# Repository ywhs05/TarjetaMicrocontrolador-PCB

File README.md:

# TarjetaMicrocontrolador-PCB

### Descripción
PCB que facilita la conexión con el microcontrolador LAUNCHXL-F28379D.

Proyecto del laboratorio LabCES de la Universidad de Costa Rica.

Permite facilitar la conexión con el microcontrolador LAUNCHXL-F28379D con las otras placas modulares:
- [Tarjeta digital a fibra óptica (DaFO)](https://github.com/ywhs05/DigitalToFiberOpticConverter-PCB)
- [Tarjeta sensor](https://github.com/ywhs05/TarjetaSensor-PCB)

Esta PCB es la tarjeta principal del sistema modular, tendrá la alimentación para las placas y el microcontrolador.

### Soporte
- y.huang@ucr.ac.cr
- mauricio.espinoza_bola@ucr.ac.cr

### Estado del proyecto

Se encuentra proceso de revisión en la etapa del diagrama esquemático y PCB.

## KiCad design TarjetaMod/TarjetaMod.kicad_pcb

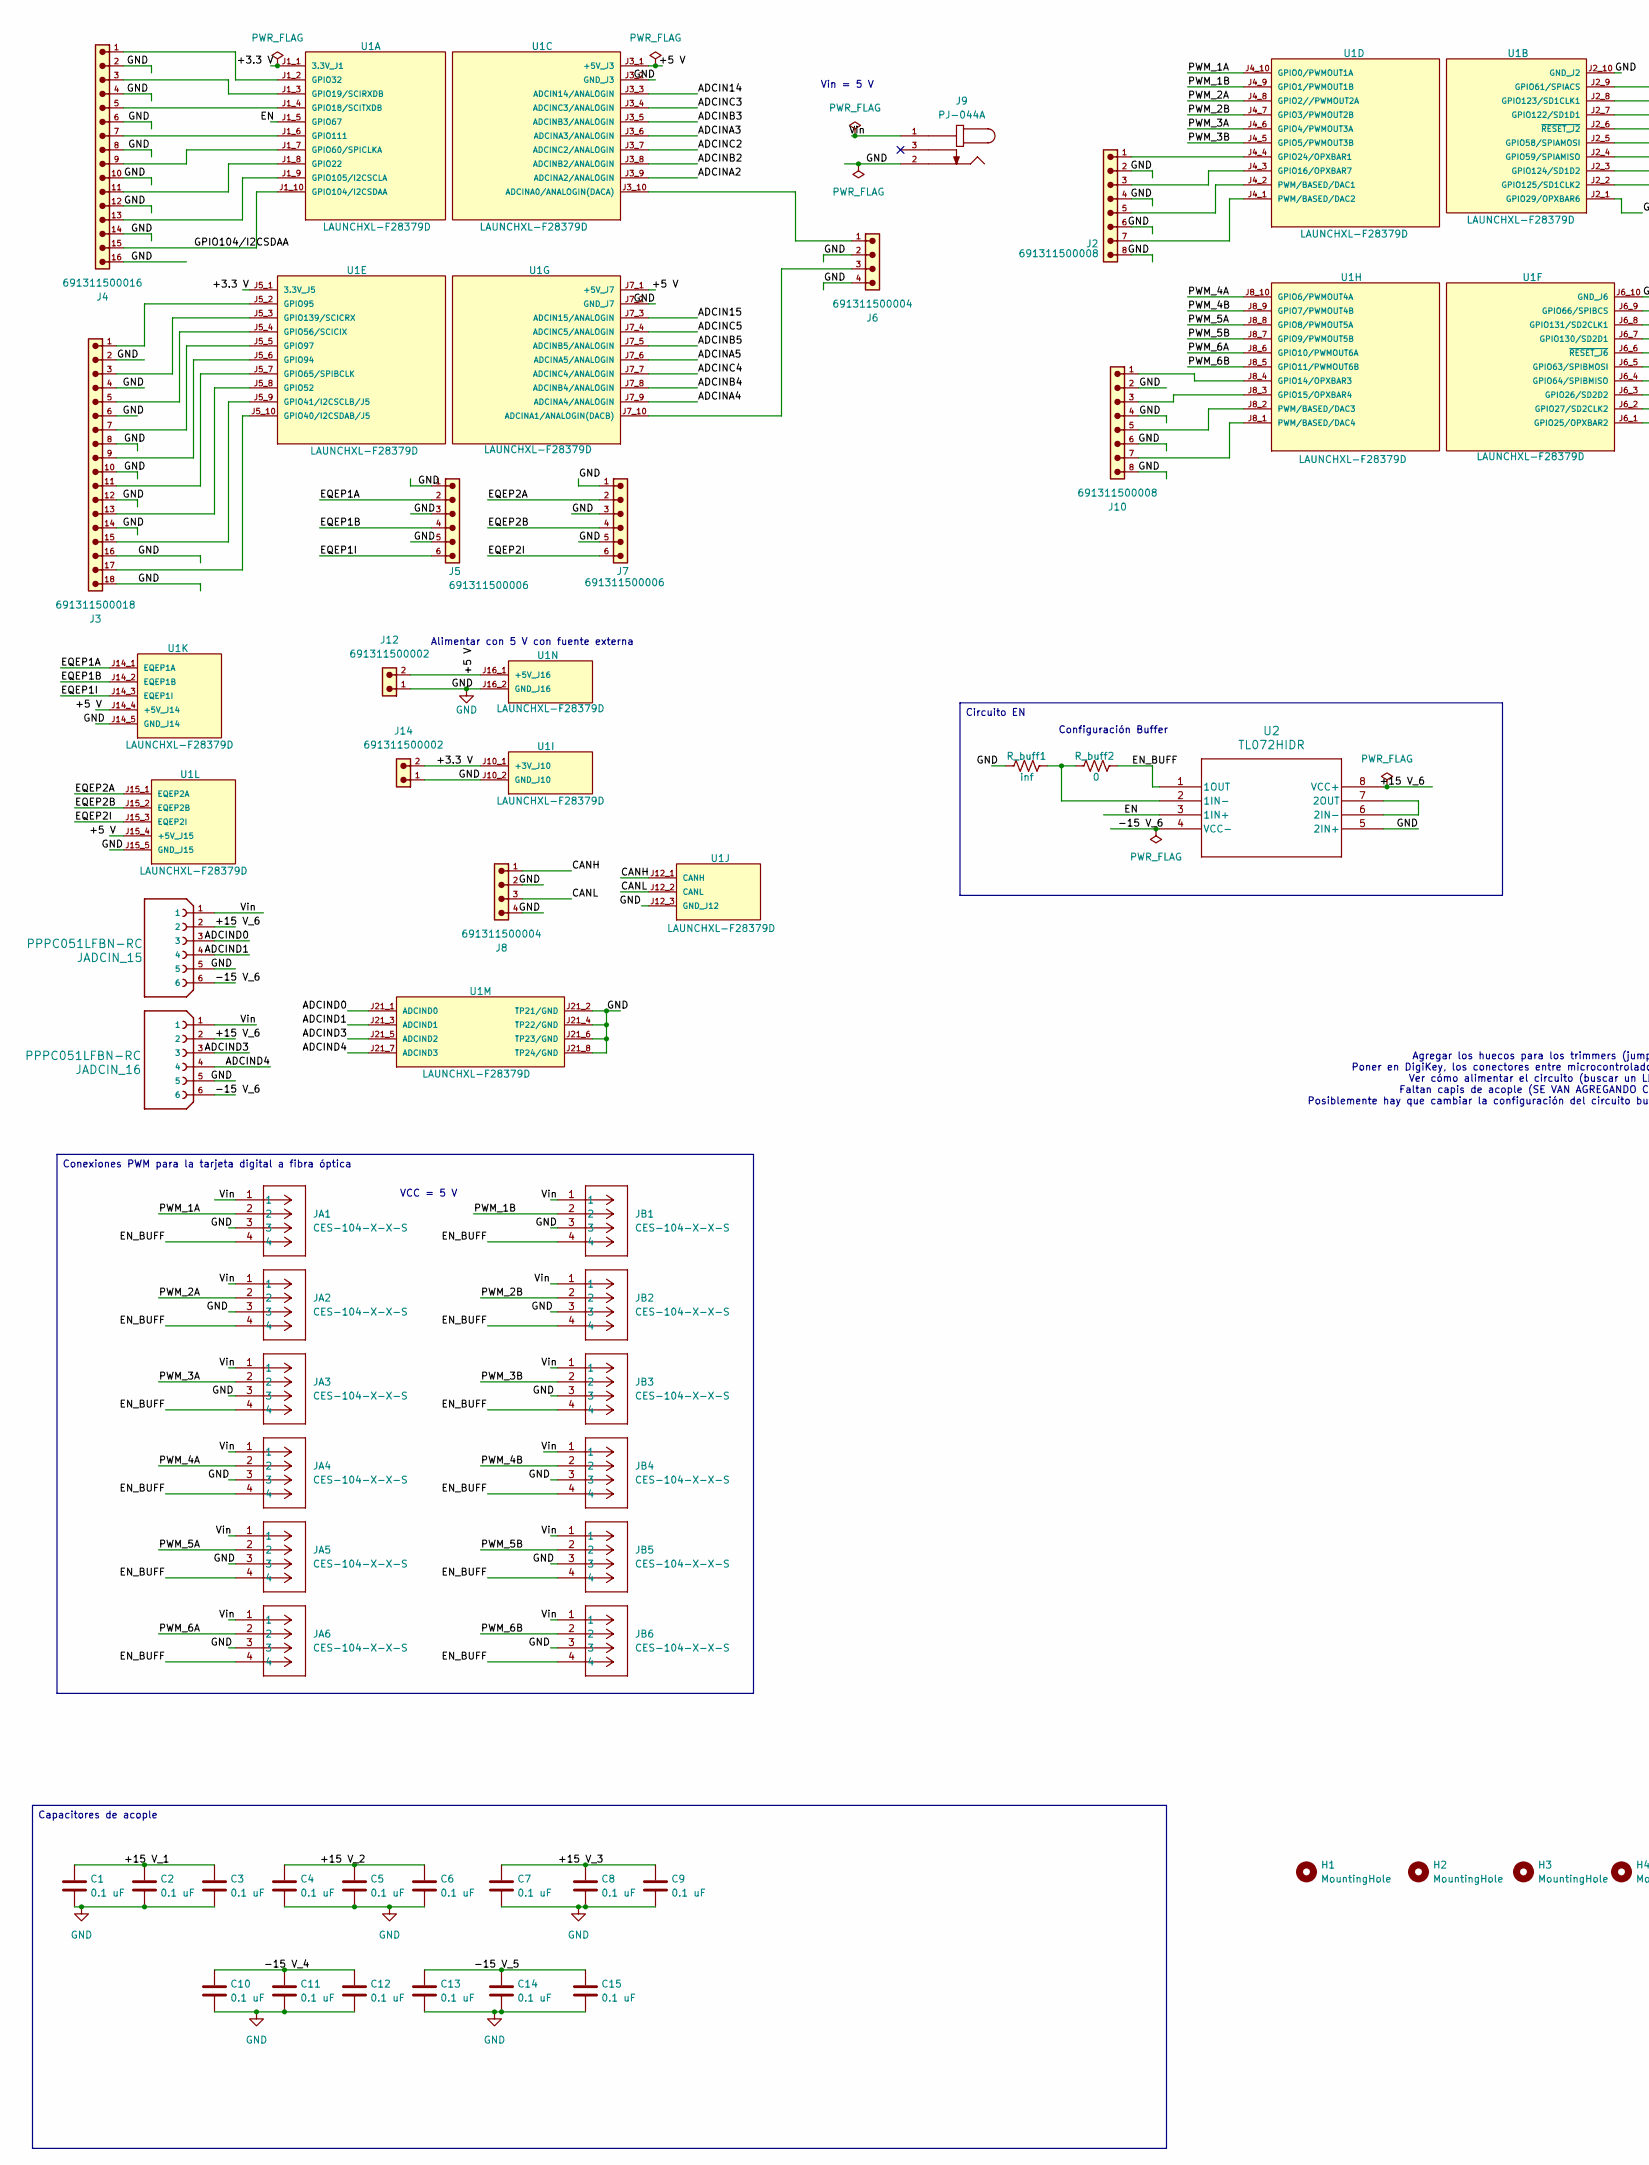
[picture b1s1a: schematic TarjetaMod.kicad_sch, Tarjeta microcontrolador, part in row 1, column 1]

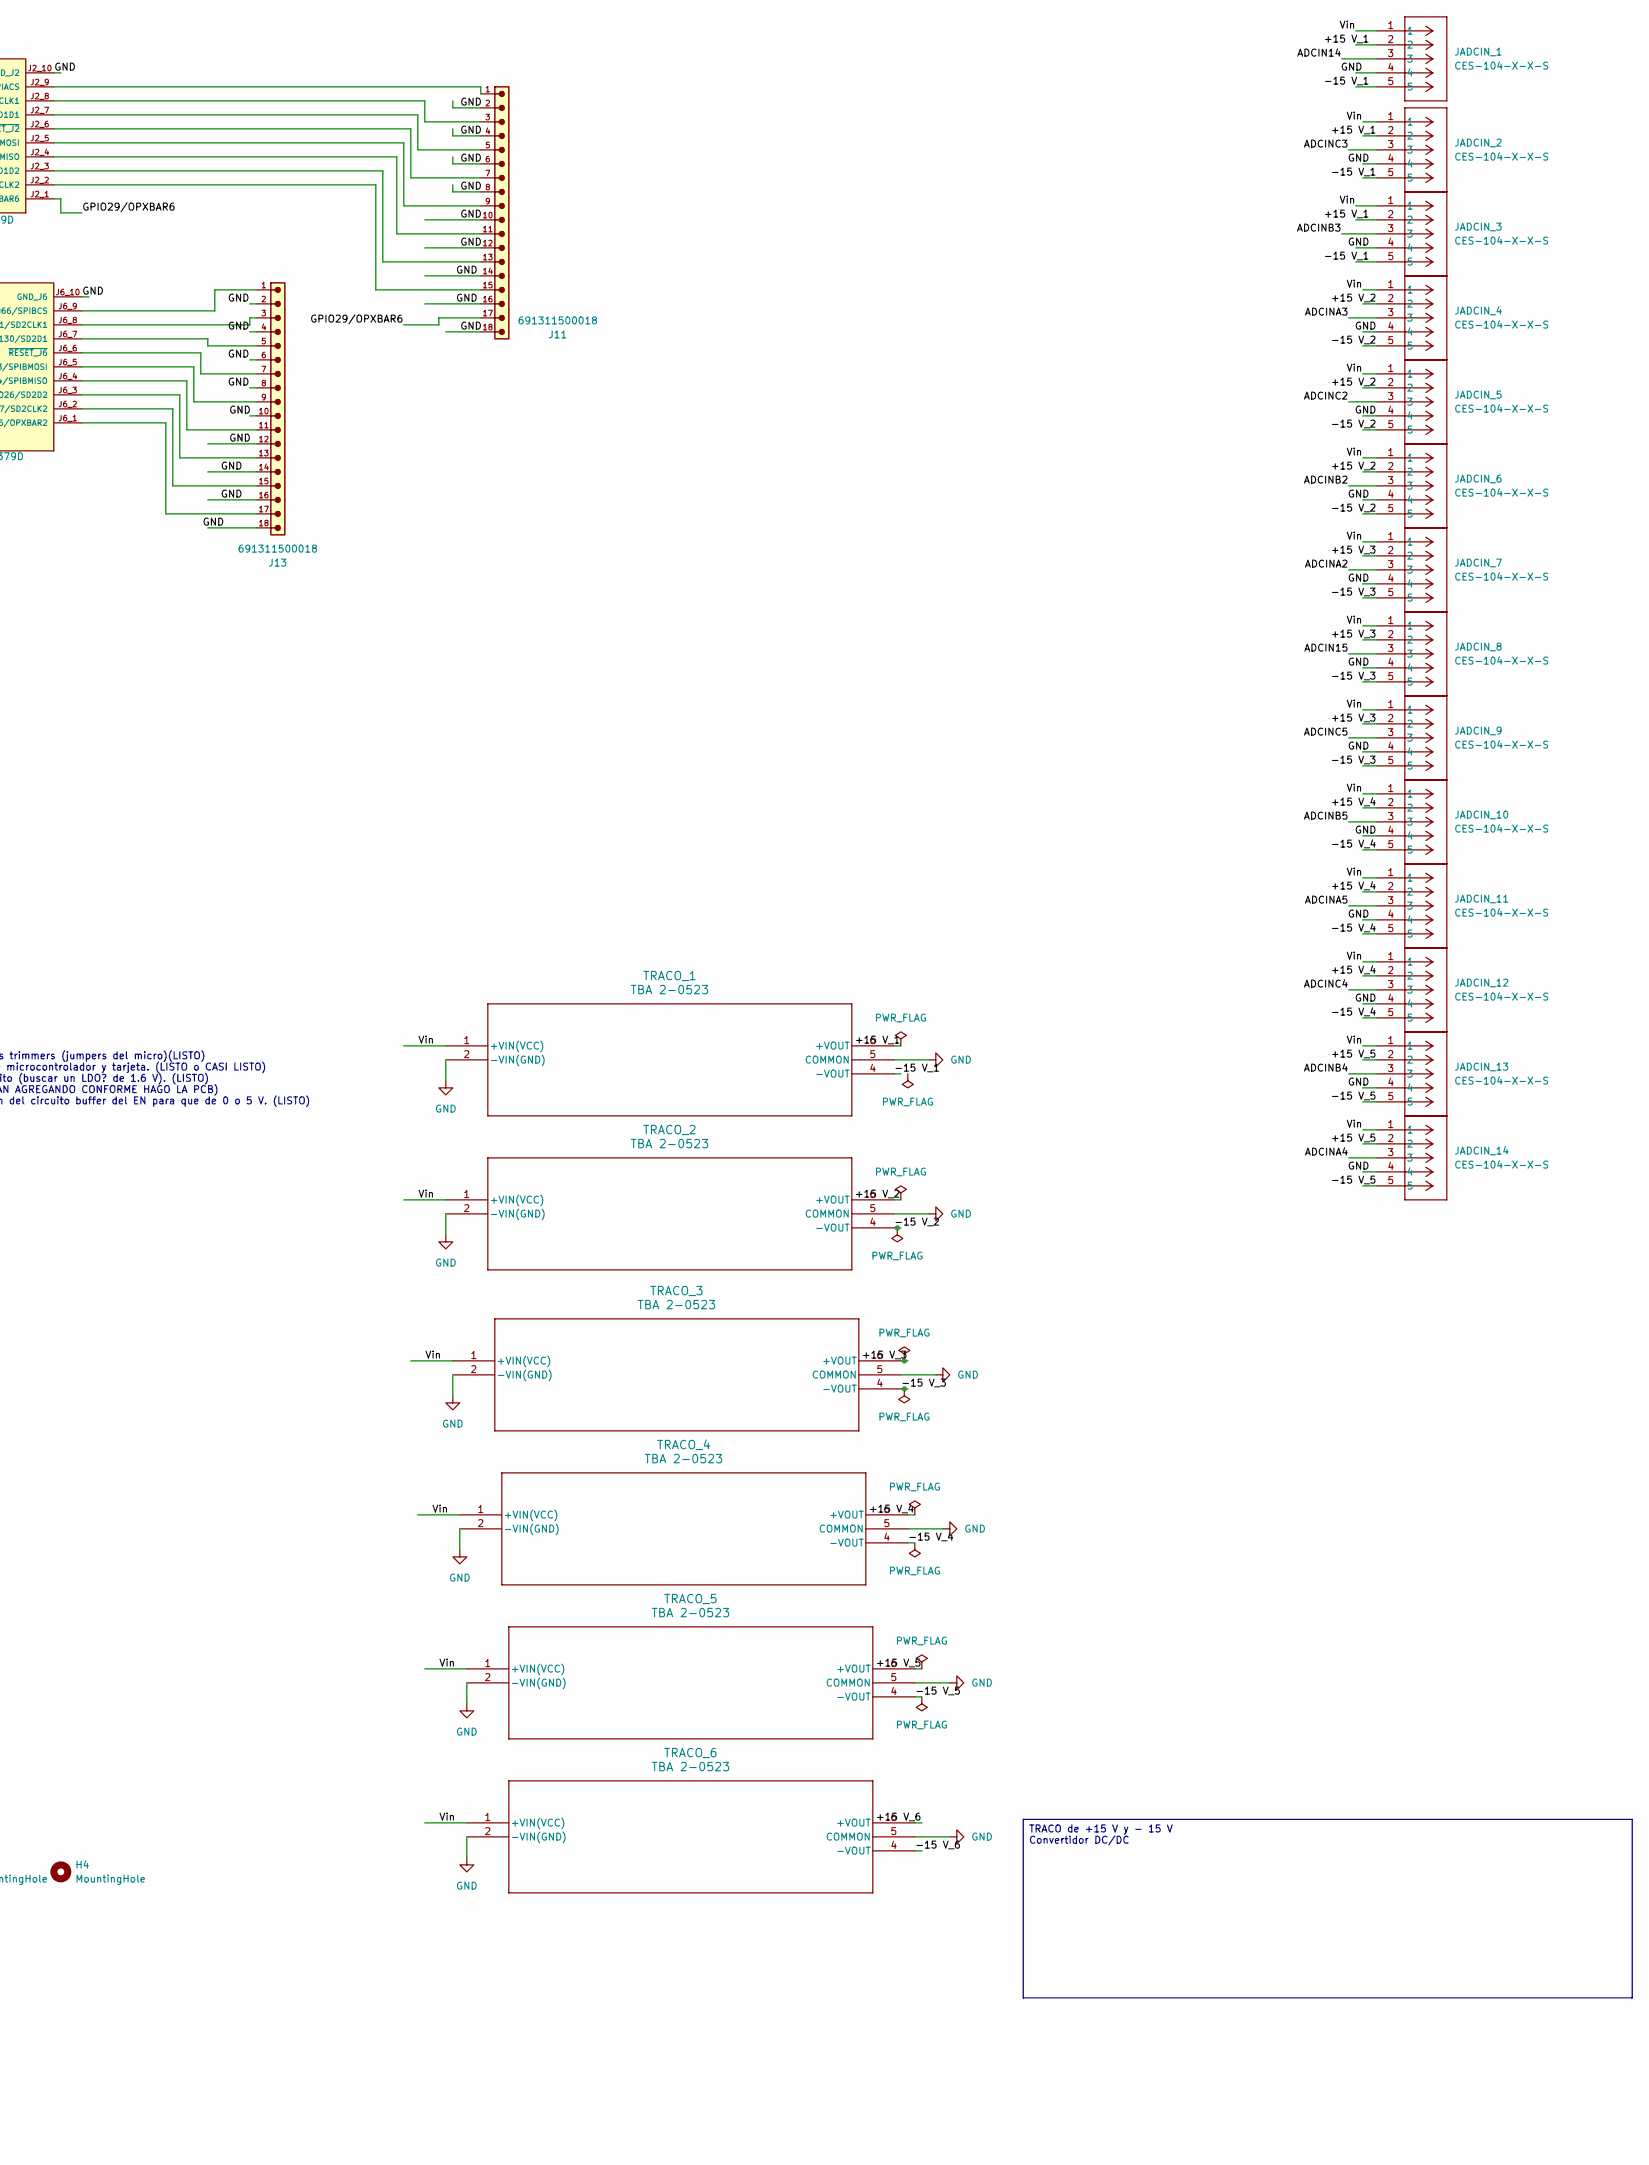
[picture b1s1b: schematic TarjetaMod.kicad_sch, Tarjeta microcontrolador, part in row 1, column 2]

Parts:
C1, C2, C3, C4, C5, C6, C7, C8, C9, C10, C11, C12, C13, C14, C15: 0.1 uF; C_1206_3216Metric_Pad1.33x1.80mm_HandSolder
H1, H2, H3, H4: MountingHole; MountingHole_3.2mm_M3
J2, J10: 691311500008
J3, J11, J13: 691311500018; DigiKey_Part_Number 732-691311500018-ND
J4: 691311500016; DigiKey_Part_Number 732-691311500016-ND
J5, J7: 691311500006; DigiKey_Part_Number 732-2056-ND
J6, J8: 691311500004; DigiKey_Part_Number 732-2054-ND
J9: PJ-044A; CUI_PJ-044A; PARTREV 1.02
J12, J14: 691311500002; DigiKey_Part_Number 732-2052-ND
JA1, JA2, JA3, JA4, JA5, JA6: CES-104-X-X-S; SULLINS_PPTC041LFBN-RC; PARTREV A
JADCIN_1, JADCIN_2, JADCIN_3, JADCIN_4, JADCIN_5, JADCIN_6, JADCIN_7, JADCIN_8, JADCIN_9, JADCIN_10, JADCIN_11, JADCIN_12, JADCIN_13, JADCIN_14: CES-104-X-X-S; CONN_PPPC051LFBN-RC_SUL; PARTREV A
JADCIN_15, JADCIN_16: PPPC051LFBN-RC; SULLINS_PPTC061LFBN-RC; PARTREV L
JB1, JB2, JB3, JB4, JB5, JB6: CES-104-X-X-S; SULLINS_PPTC041LFBN-RC; PARTREV A
R_buff1: inf; R_1206_3216Metric_Pad1.30x1.75mm_HandSolder
R_buff2: 0; R_1206_3216Metric_Pad1.30x1.75mm_HandSolder
TRACO_1, TRACO_2, TRACO_3, TRACO_4, TRACO_5, TRACO_6: TBA 2-0523; RELAY_TBA 2_TRP
U1: LAUNCHXL-F28379D; MOD_LAUNCHXL-F28379D; PARTREV 2.0
U2: TL072HIDR; SOIC8_D_TEX

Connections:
/+3.3 V: J14.2, U1.J1_1 (3.3V_J1), U1.J5_1 (3.3V_J5), U1.J10_1 (+3V_J10)
/+5 V: J12.2, U1.J3_1 (+5V_J3), U1.J7_1 (+5V_J7), U1.J14_4 (+5V_J14), U1.J15_4 (+5V_J15), U1.J16_1 (+5V_J16)
/+15 V_1: C1.1, C2.1, C3.1, JADCIN_1.2, JADCIN_2.2, JADCIN_3.2, TRACO_1.6 (+VOUT)
/+15 V_2: C4.1, C5.1, C6.1, JADCIN_4.2, JADCIN_5.2, JADCIN_6.2, TRACO_2.6 (+VOUT)
/+15 V_3: C7.1, C8.1, C9.1, JADCIN_7.2, JADCIN_8.2, JADCIN_9.2, TRACO_3.6 (+VOUT)
/+15 V_4: JADCIN_10.2, JADCIN_11.2, JADCIN_12.2, TRACO_4.6 (+VOUT)
/+15 V_5: JADCIN_13.2, JADCIN_14.2, TRACO_5.6 (+VOUT)
/+15 V_6: JADCIN_15.2, JADCIN_16.2, TRACO_6.6 (+VOUT), U2.8 (VCC+)
/-15 V_1: JADCIN_1.5, JADCIN_2.5, JADCIN_3.5, TRACO_1.4 (-VOUT)
/-15 V_2: JADCIN_4.5, JADCIN_5.5, JADCIN_6.5, TRACO_2.4 (-VOUT)
/-15 V_3: JADCIN_7.5, JADCIN_8.5, JADCIN_9.5, TRACO_3.4 (-VOUT)
/-15 V_4: C10.1, C11.1, C12.1, JADCIN_10.5, JADCIN_11.5, JADCIN_12.5, TRACO_4.4 (-VOUT)
/-15 V_5: C13.1, C14.1, C15.1, JADCIN_13.5, JADCIN_14.5, TRACO_5.4 (-VOUT)
/-15 V_6: JADCIN_15.6, JADCIN_16.6, TRACO_6.4 (-VOUT), U2.4 (VCC-)
/ADCIN14: JADCIN_1.3, U1.J3_3 (ADCIN14/ANALOGIN)
/ADCIN15: JADCIN_8.3, U1.J7_3 (ADCIN15/ANALOGIN)
/ADCINA2: JADCIN_7.3, U1.J3_9 (ADCINA2/ANALOGIN)
/ADCINA3: JADCIN_4.3, U1.J3_6 (ADCINA3/ANALOGIN)
/ADCINA4: JADCIN_14.3, U1.J7_9 (ADCINA4/ANALOGIN)
/ADCINA5: JADCIN_11.3, U1.J7_6 (ADCINA5/ANALOGIN)
/ADCINB2: JADCIN_6.3, U1.J3_8 (ADCINB2/ANALOGIN)
/ADCINB3: JADCIN_3.3, U1.J3_5 (ADCINB3/ANALOGIN)
/ADCINB4: JADCIN_13.3, U1.J7_8 (ADCINB4/ANALOGIN)
/ADCINB5: JADCIN_10.3, U1.J7_5 (ADCINB5/ANALOGIN)
/ADCINC2: JADCIN_5.3, U1.J3_7 (ADCINC2/ANALOGIN)
/ADCINC3: JADCIN_2.3, U1.J3_4 (ADCINC3/ANALOGIN)
/ADCINC4: JADCIN_12.3, U1.J7_7 (ADCINC4/ANALOGIN)
/ADCINC5: JADCIN_9.3, U1.J7_4 (ADCINC5/ANALOGIN)
/ADCIND0: JADCIN_15.3, U1.J21_1 (ADCIND0)
/ADCIND1: JADCIN_15.4, U1.J21_3 (ADCIND1)
/ADCIND3: JADCIN_16.3, U1.J21_5 (ADCIND2)
/ADCIND4: JADCIN_16.4, U1.J21_7 (ADCIND3)
/CANH: J8.1, U1.J12_1 (CANH)
/CANL: J8.3, U1.J12_2 (CANL)
/EN: U1.J1_5 (GPIO67), U2.3 (1IN+)
/EN_BUFF: JA1.4, JA2.4, JA3.4, JA4.4, JA5.4, JA6.4, JB1.4, JB2.4, JB3.4, JB4.4, JB5.4, JB6.4, R_buff2.1, U2.1 (1OUT)
/EQEP1A: J5.2, U1.J14_1 (EQEP1A)
/EQEP1B: J5.4, U1.J14_2 (EQEP1B)
/EQEP1I: J5.6, U1.J14_3 (EQEP1I)
/EQEP2A: J7.2, U1.J15_1 (EQEP2A)
/EQEP2B: J7.4, U1.J15_2 (EQEP2B)
/EQEP2I: J7.6, U1.J15_3 (EQEP2I)
/GPIO29/OPXBAR6: J11.17, U1.J2_1 (GPIO29/OPXBAR6)
/GPIO104/I2CSDAA: J4.15, U1.J1_10 (GPIO104/I2CSDAA)
/PWM_1A: JA1.2, U1.J4_10 (GPIO0/PWMOUT1A)
/PWM_1B: JB1.2, U1.J4_9 (GPIO1/PWMOUT1B)
/PWM_2A: JA2.2, U1.J4_8 (GPIO2//PWMOUT2A)
/PWM_2B: JB2.2, U1.J4_7 (GPIO3/PWMOUT2B)
/PWM_3A: JA3.2, U1.J4_6 (GPIO4/PWMOUT3A)
/PWM_3B: JB3.2, U1.J4_5 (GPIO5/PWMOUT3B)
/PWM_4A: JA4.2, U1.J8_10 (GPIO6/PWMOUT4A)
/PWM_4B: JB4.2, U1.J8_9 (GPIO7/PWMOUT4B)
/PWM_5A: JA5.2, U1.J8_8 (GPIO8/PWMOUT5A)
/PWM_5B: JB5.2, U1.J8_7 (GPIO9/PWMOUT5B)
/PWM_6A: JA6.2, U1.J8_6 (GPIO10/PWMOUT6A)
/PWM_6B: JB6.2, U1.J8_5 (GPIO11/PWMOUT6B)
/Vin: J9.1, JA1.1, JA2.1, JA3.1, JA4.1, JA5.1, JA6.1, JADCIN_1.1, JADCIN_2.1, JADCIN_3.1, JADCIN_4.1, JADCIN_5.1, JADCIN_6.1, JADCIN_7.1, JADCIN_8.1, JADCIN_9.1, JADCIN_10.1, JADCIN_11.1, JADCIN_12.1, JADCIN_13.1, JADCIN_14.1, JADCIN_15.1, JADCIN_16.1, JB1.1, JB2.1, JB3.1, JB4.1, JB5.1, JB6.1, TRACO_1.1 (+VIN(VCC)), TRACO_2.1 (+VIN(VCC)), TRACO_3.1 (+VIN(VCC)), TRACO_4.1 (+VIN(VCC)), TRACO_5.1 (+VIN(VCC)), TRACO_6.1 (+VIN(VCC))
GND: C1.2, C2.2, C3.2, C4.2, C5.2, C6.2, C7.2, C8.2, C9.2, C10.2, C11.2, C12.2, C13.2, C14.2, C15.2, J2.2, J2.4, J2.6, J2.8, J3.2, J3.4, J3.6, J3.8, J3.10, J3.12, J3.14, J3.16, J3.18, J4.2, J4.4, J4.6, J4.8, J4.10, J4.12, J4.14, J4.16, J5.1, J5.3, J5.5, J6.2, J6.4, J7.1, J7.3, J7.5, J8.2, J8.4, J9.2, J10.2, J10.4, J10.6, J10.8, J11.2, J11.4, J11.6, J11.8, J11.10, J11.12, J11.14, J11.16, J11.18, J12.1, J13.2, J13.4, J13.6, J13.8, J13.10, J13.12, J13.14, J13.16, J13.18, J14.1, JA1.3, JA2.3, JA3.3, JA4.3, JA5.3, JA6.3, JADCIN_1.4, JADCIN_2.4, JADCIN_3.4, JADCIN_4.4, JADCIN_5.4, JADCIN_6.4, JADCIN_7.4, JADCIN_8.4, JADCIN_9.4, JADCIN_10.4, JADCIN_11.4, JADCIN_12.4, JADCIN_13.4, JADCIN_14.4, JADCIN_15.5, JADCIN_16.5, JB1.3, JB2.3, JB3.3, JB4.3, JB5.3, JB6.3, R_buff1.2, TRACO_1.2 (-VIN(GND)), TRACO_1.5 (COMMON), TRACO_2.2 (-VIN(GND)), TRACO_2.5 (COMMON), TRACO_3.2 (-VIN(GND)), TRACO_3.5 (COMMON), TRACO_4.2 (-VIN(GND)), TRACO_4.5 (COMMON), TRACO_5.2 (-VIN(GND)), TRACO_5.5 (COMMON), TRACO_6.2 (-VIN(GND)), TRACO_6.5 (COMMON), U1.J2_10 (GND_J2), U1.J3_2 (GND_J3), U1.J6_10 (GND_J6), U1.J7_2 (GND_J7), U1.J10_2 (GND_J10), U1.J10_3 (GND_J10), U1.J12_3 (GND_J12), U1.J14_5 (GND_J14), U1.J15_5 (GND_J15), U1.J16_2 (GND_J16), U1.J16_3 (GND_J16), U1.J21_2 (TP21/GND), U1.J21_4 (TP22/GND), U1.J21_6 (TP23/GND), U1.J21_8 (TP24/GND), U2.5 (2IN+)
unnamed: J4.5, U1.J1_4 (GPIO18/SCITXDB)
unnamed: J4.3, U1.J1_3 (GPIO19/SCIRXDB)
unnamed: J4.11, U1.J1_8 (GPIO22)
unnamed: J4.1, U1.J1_2 (GPIO32)
unnamed: J4.9, U1.J1_7 (GPIO60/SPICLKA)
unnamed: J4.13, U1.J1_9 (GPIO105/I2CSCLA)
unnamed: J4.7, U1.J1_6 (GPIO111)
unnamed: J11.9, U1.J2_5 (GPIO58/SPIAMOSI)
unnamed: J11.11, U1.J2_4 (GPIO59/SPIAMISO)
unnamed: J11.1, U1.J2_9 (GPIO61/SPIACS)
unnamed: J11.5, U1.J2_7 (GPIO122/SD1D1)
unnamed: J11.3, U1.J2_8 (GPIO123/SD1CLK1)
unnamed: J11.13, U1.J2_3 (GPIO124/SD1D2)
unnamed: J11.15, U1.J2_2 (GPIO125/SD1CLK2)
unnamed: J11.7, U1.J2_6 (~RESET_J2)
unnamed: J6.1, U1.J3_10 (ADCINA0/ANALOGIN(DACA))
unnamed: J2.3, U1.J4_3 (GPIO16/OPXBAR7)
unnamed: J2.1, U1.J4_4 (GPIO24/OPXBAR1)
unnamed: J2.5, U1.J4_2 (PWM/BASED/DAC1)
unnamed: J2.7, U1.J4_1 (PWM/BASED/DAC2)
unnamed: J3.17, U1.J5_10 (GPIO40/I2CSDAB/J5)
unnamed: J3.15, U1.J5_9 (GPIO41/I2CSCLB/J5)
unnamed: J3.13, U1.J5_8 (GPIO52)
unnamed: J3.5, U1.J5_4 (GPIO56/SCICIX)
unnamed: J3.11, U1.J5_7 (GPIO65/SPIBCLK)
unnamed: J3.9, U1.J5_6 (GPIO94)
unnamed: J3.1, U1.J5_2 (GPIO95)
unnamed: J3.7, U1.J5_5 (GPIO97)
unnamed: J3.3, U1.J5_3 (GPIO139/SCICRX)
unnamed: J13.17, U1.J6_1 (GPIO25/OPXBAR2)
unnamed: J13.13, U1.J6_3 (GPIO26/SD2D2)
unnamed: J13.15, U1.J6_2 (GPIO27/SD2CLK2)
unnamed: J13.9, U1.J6_5 (GPIO63/SPIBMOSI)
unnamed: J13.11, U1.J6_4 (GPIO64/SPIBMISO)
unnamed: J13.1, U1.J6_9 (GPIO66/SPIBCS)
unnamed: J13.5, U1.J6_7 (GPIO130/SD2D1)
unnamed: J13.3, U1.J6_8 (GPIO131/SD2CLK1)
unnamed: J13.7, U1.J6_6 (~RESET_J6)
unnamed: J6.3, U1.J7_10 (ADCINA1/ANALOGIN(DACB))
unnamed: J10.1, U1.J8_4 (GPIO14/OPXBAR3)
unnamed: J10.3, U1.J8_3 (GPIO15/OPXBAR4)
unnamed: J10.5, U1.J8_2 (PWM/BASED/DAC3)
unnamed: J10.7, U1.J8_1 (PWM/BASED/DAC4)
unnamed: R_buff1.1, R_buff2.2, U2.2 (1IN-)
unnamed: U2.6 (2IN-), U2.7 (2OUT)

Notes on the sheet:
Agregar los huecos para los trimmers (jumpers del micro)(LISTO) Poner en DigiKey, los conectores entre microcontrolador y tarjeta. (LISTO o CASI LISTO) Ver cómo alimentar el circuito (buscar un LDO? de 1.6 V). (LISTO) Faltan capis de acople (SE VAN AGREGANDO CONFORME HAGO LA PCB) Posiblemente hay q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
Configuración Buffer
VCC = 5 V
Vin = 5 V
Alimentar con 5 V con fuente externa
Circuito EN
Conexiones PWM para la tarjeta digital a fibra óptica
Capacitores de acople
TRACO de +15 V y - 15 V Convertidor DC/DC

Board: 4 copper layers, 70 parts (0 on the bottom side), 103 nets, no tracks yet.

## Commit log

2026-06-28 Archivos de KiCad de la tarjeta microcontrolador y actualización del README.md.
2026-06-28 Adición de serigrafía sobre señal EN en la PCB.
2026-06-28 Acomodo de componentes en el diagrama esquemático.
